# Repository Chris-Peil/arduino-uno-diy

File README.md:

# arduino-uno-diy
Altium to KiCad project conversion

https://docs.arduino.cc/hardware/make-your-uno-kit/

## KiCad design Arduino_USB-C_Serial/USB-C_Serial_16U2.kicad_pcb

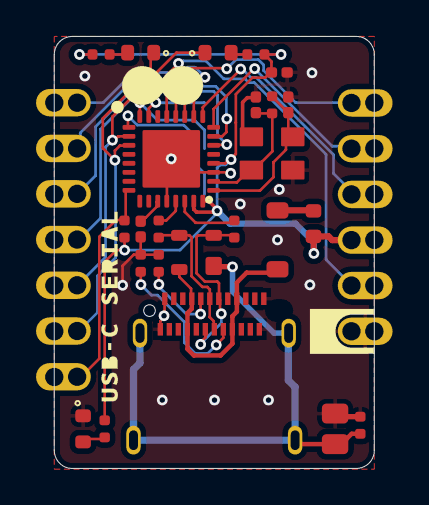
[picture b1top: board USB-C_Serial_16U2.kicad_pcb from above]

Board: 2 copper layers, 17.8 x 24.0 mm, 27 parts (1 on the bottom side), 31 nets.

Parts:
C1: C0402C105K8PACTU; CAP-0402
C2: C0805C472KDRACTU; CAP-0805
C3, C4: C0402H100J5GACTU; CAP-0402
C5: C0402C104K4RACTU; CAP-0402
D1: PRTR5V0U2X,215; SOT190P230X110-4N
D2: PMEG6020AELRX; SOD123-1
DL1, DL2: HSMD-C190; LEDC1608X80N-AK
DL3: HSMG-C190; LEDC1608X80N-AK
ICPS1: PINHD-2X03-SM-TP; _ProgramData_Altium_Altium Designer {48FE0314-AEBD-4D04-941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
J1: 12401598E4#2A
J2: PH1-07-UA; CONN STRIP 2.54 PIN HEADER DIP 180° 1x 7 PIN GOLD FLASH cas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
J3: PH1-06-UA; CONN STRP 2.54 PIN HEADER DIP 180° 1x X PIN GOLD FLASH
L1: BLM18PG471SN1D; L-0603
R1, R2: RC0402FR-075K1L; RES-0402
R3, R6: CRCW04021M00FKED; RES-0402
R4, R5: CRCW040222R0JNEDC; RES-0402
R7: CRCW040210K0FKED; RES-0402
R8, R9, R10: CRCW0402330RJNED; RES-0402
U1: ATMEGA16U2; ATMEL_QFN32
Y1: FTX16.000M12SM3S-30/30; CX3225SB16000D0GZJC1-Footprint-1

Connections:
CD: J2.4, U1.6
CTS: J3.2, U1.13
D+: D1.3, J1.A6, J1.B6, R5.1
D-: D1.2, J1.A7, J1.B7, R4.1
DSR: J2.2, U1.11
DTR: J2.1, U1.10
GND: C1.2, C2.1, C3.1, C4.1, C5.1, DL3.C, J1.A1, J1.A12, J1.B1, J1.B12, J3.1, R1.1, R2.2, R3.1, U1.3, U1.28, U1.EXP, Y1.2, Y1.4
LED_RX: DL1.C, J2.5, U1.18
LED_TX: DL2.C, J2.6, U1.19
MISO: ICPS1.5, U1.17
MOSI: ICPS1.3, U1.16
NetC1_1: C1.1, U1.27
NetC2_2: C2.2, D1.1, J1.SHIELD 1, J1.SHIELD 2, J1.SHIELD 3, J1.SHIELD 4, R3.2
NetC3_2: C3.2, R6.2, U1.2, Y1.3
NetC4_2: C4.2, R6.1, U1.1, Y1.1
NetD2_C: D2.C, L1.1
NetDL1_A: DL1.A, R9.1
NetDL2_A: DL2.A, R8.2
NetDL3_A: DL3.A, R10.1
NetJ1_A5: J1.A5, R1.2
NetJ1_B5: J1.B5, R2.1
NetR4_2: R4.2, U1.30
NetR5_2: R5.2, U1.29
RI: J2.3, U1.7
RST: J2.7, R7.1, U1.24
RTS: J3.6, U1.12
RXD: J3.5, U1.8
SCLK: ICPS1.1, U1.15
TXD: J3.4, U1.9
VBUS: D1.4, D2.A, J1.A4, J1.A9, J1.B4, J1.B9
VCC: C5.2, J3.3, L1.2, R7.2, R8.1, R9.2, R10.2, U1.4, U1.31, U1.32

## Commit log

2025-08-04 initial
